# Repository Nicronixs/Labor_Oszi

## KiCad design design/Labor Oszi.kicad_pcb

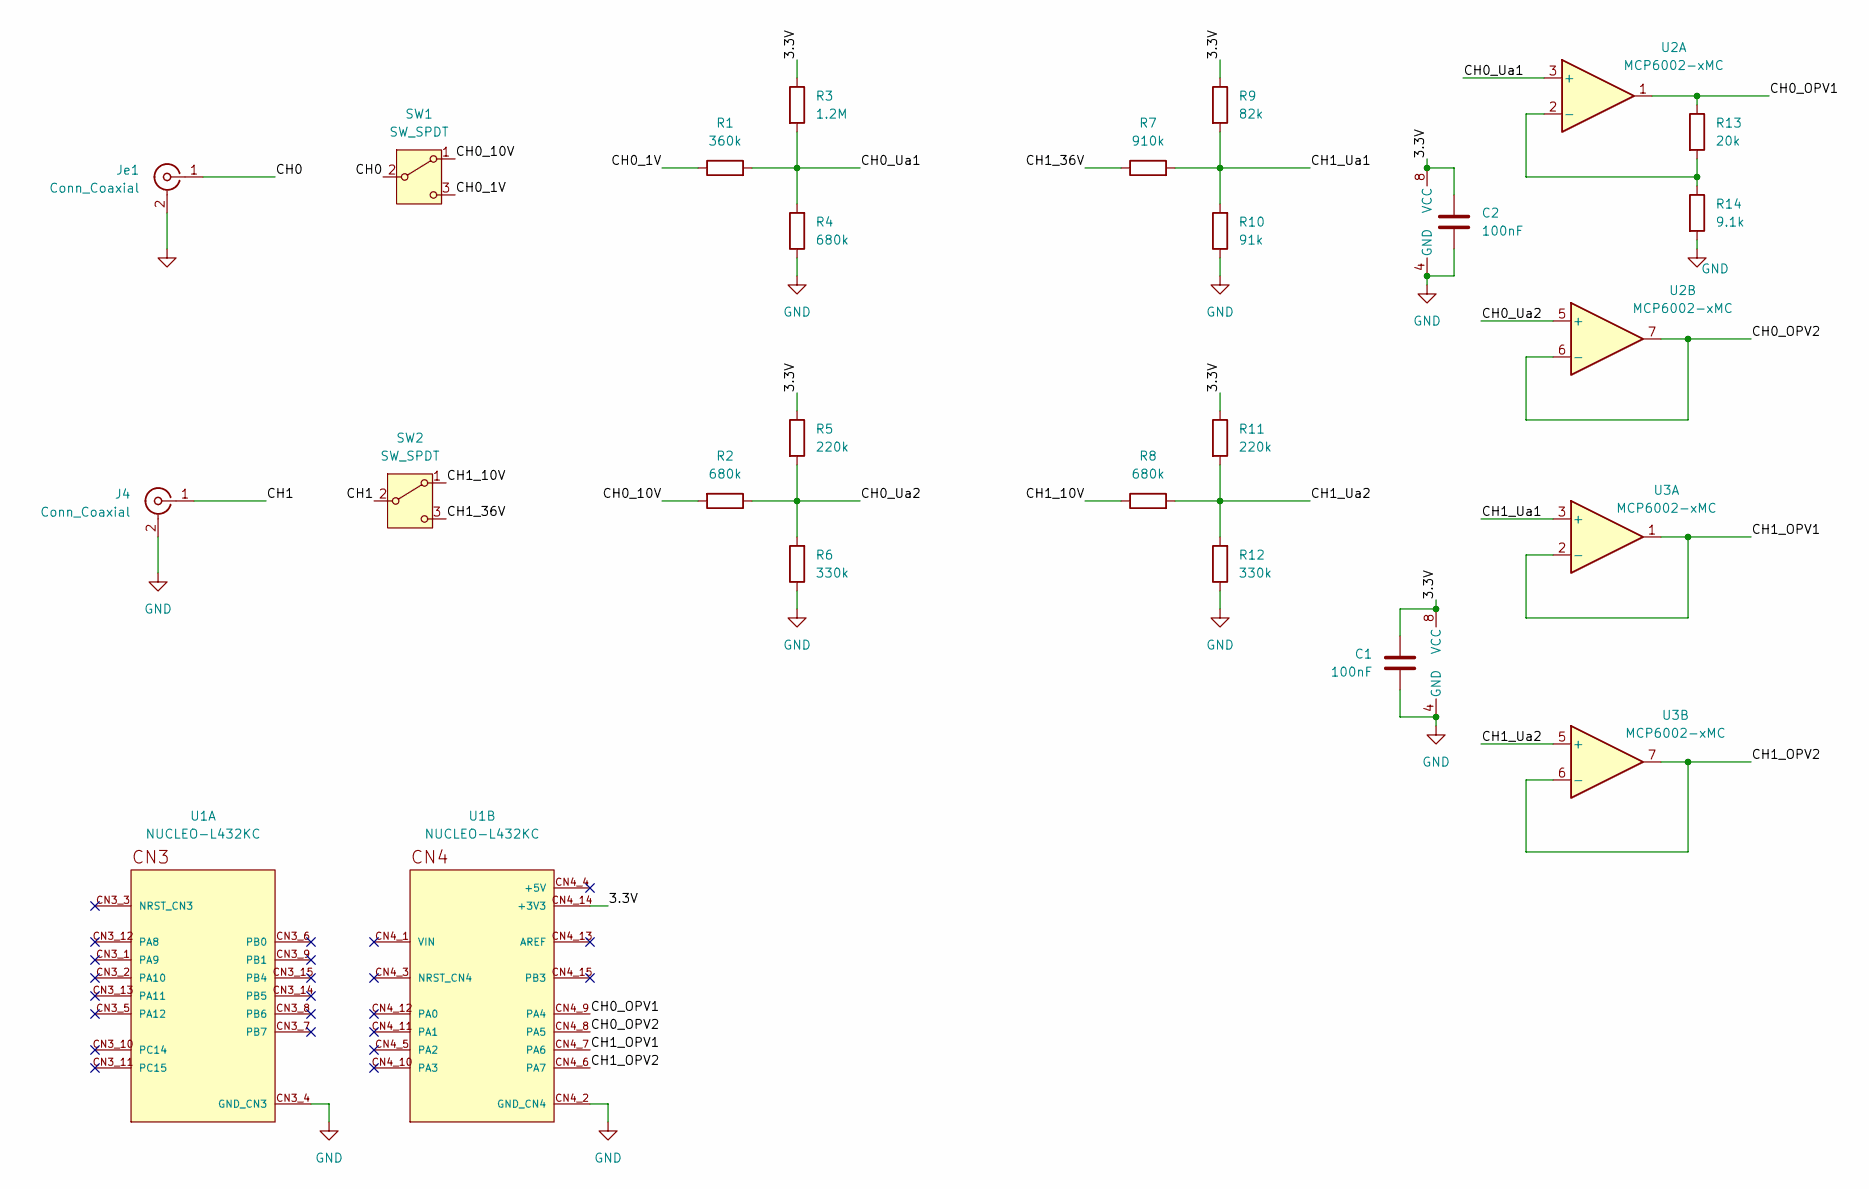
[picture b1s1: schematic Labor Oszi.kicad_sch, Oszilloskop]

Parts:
C1, C2: 100nF; C_0603_1608Metric_Pad1.08x0.95mm_HandSolder; LCSC Part # C14663
J4: Conn_Coaxial; LINX_CONBNC001
Je1: Conn_Coaxial; LINX_CONBNC001
R1: 360k; R_0603_1608Metric_Pad0.98x0.95mm_HandSolder; LCSC Part # C23146
R2, R4, R8: 680k; R_0603_1608Metric_Pad0.98x0.95mm_HandSolder; LCSC Part # C25822
R3: 1.2M; R_0603_1608Metric_Pad0.98x0.95mm_HandSolder; LCSC Part # C22107
R5, R11: 220k; R_0603_1608Metric_Pad0.98x0.95mm_HandSolder; LCSC Part # C22961
R6, R12: 330k; R_0603_1608Metric_Pad0.98x0.95mm_HandSolder; LCSC Part # C23137
R7: 910k; R_0603_1608Metric_Pad0.98x0.95mm_HandSolder; LCSC Part # C23263
R9: 82k; R_0603_1608Metric_Pad0.98x0.95mm_HandSolder; LCSC Part # C23254
R10: 91k; R_0603_1608Metric_Pad0.98x0.95mm_HandSolder; LCSC Part # C23265
R13: 20k; R_0603_1608Metric_Pad0.98x0.95mm_HandSolder; LCSC Part # C4184
R14: 9.1k; R_0603_1608Metric_Pad0.98x0.95mm_HandSolder; LCSC Part # C23260
SW1, SW2: SW_SPDT; SW_SPDT_PCM12
U1: NUCLEO-L432KC; MODULE_NUCLEO-L432KC; PARTREV N/A
U2, U3: MCP6002-xMC; DFN-8-1EP_3x2mm_P0.5mm_EP1.75x1.45mm; LCSC Part # C185041

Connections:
/3.3V: C1.1, C2.1, R3.1, R5.1, R9.1, R11.1, U1.CN4_14 (+3V3), U2.8 (VCC), U3.8 (VCC)
/CH0: Je1.1 (In), SW1.2 (B)
/CH0_1V: R1.1, SW1.3 (C)
/CH0_10V: R2.2, SW1.1 (A)
/CH0_OPV1: R13.1, U1.CN4_9 (PA4), U2.1
/CH0_OPV2: U1.CN4_8 (PA5), U2.6 (-), U2.7
/CH0_Ua1: R1.2, R3.2, R4.2, U2.3 (+)
/CH0_Ua2: R2.1, R5.2, R6.2, U2.5 (+)
/CH1: J4.1 (In), SW2.2 (B)
/CH1_10V: R8.1, SW2.1 (A)
/CH1_36V: R7.1, SW2.3 (C)
/CH1_OPV1: U1.CN4_7 (PA6), U3.1, U3.2 (-)
/CH1_OPV2: U1.CN4_6 (PA7), U3.6 (-), U3.7
/CH1_Ua1: R7.2, R9.2, R10.2, U3.3 (+)
/CH1_Ua2: R8.2, R11.2, R12.2, U3.5 (+)
GND: C1.2, C2.2, J4.2 (Ext), Je1.2 (Ext), R4.1, R6.1, R10.1, R12.1, R14.2, U1.CN3_4 (GND_CN3), U1.CN4_2 (GND_CN4), U2.4 (GND), U3.4 (GND)
unnamed: R13.2, R14.1, U2.2 (-)

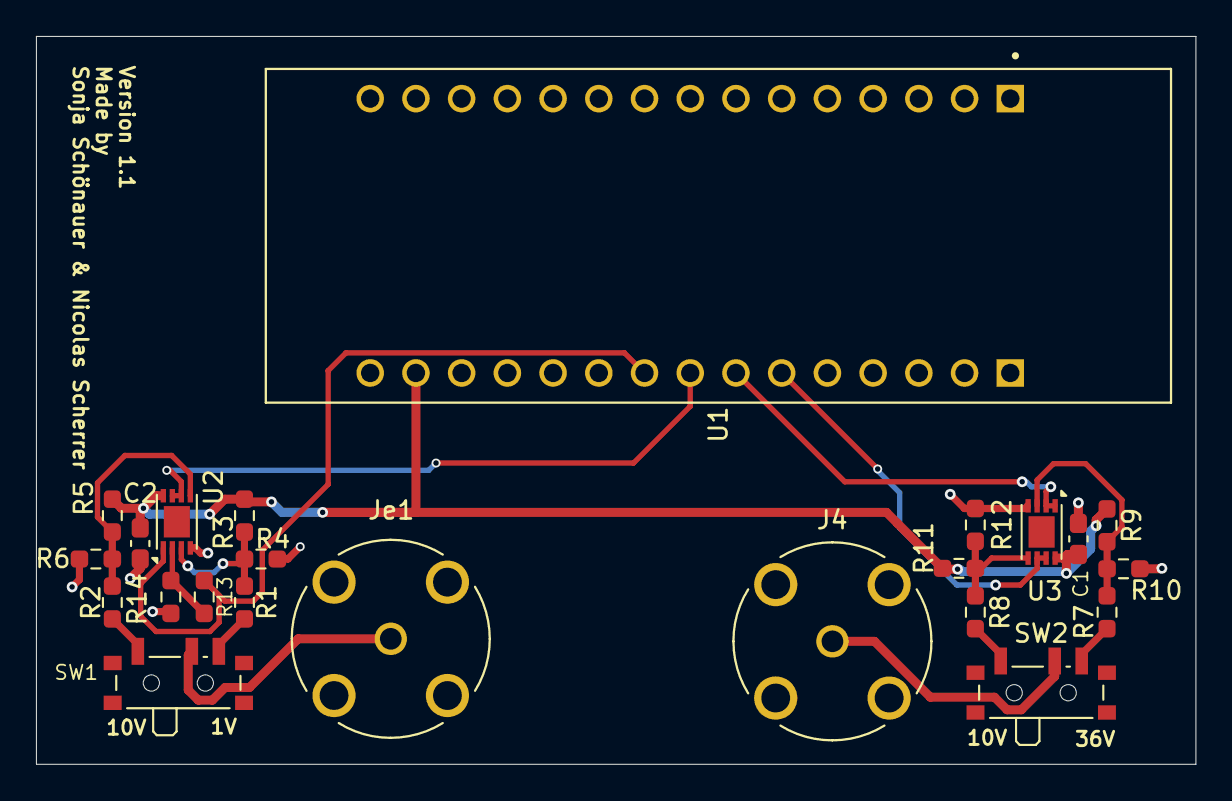
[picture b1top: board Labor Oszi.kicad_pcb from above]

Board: 2 copper layers, 64.4 x 40.4 mm, 23 parts (0 on the bottom side), 17 nets.

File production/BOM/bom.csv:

"Reference","Qty","Value","DNP","Exclude from BOM","Exclude from Board","Footprint","Datasheet","LCSC Part #"
"C1,C2","2","100nF","","","","Capacitor_SMD:C_0603_1608Metric_Pad1.08x0.95mm_HandSolder","~","C14663"
"J4,Je1","2","Conn_Coaxial","","","","CONBNC001:LINX_CONBNC001","~",""
"R1","1","360k","","","","Resistor_SMD:R_0603_1608Metric_Pad0.98x0.95mm_HandSolder","~","C23146"
"R2,R4,R8","3","680k","","","","Resistor_SMD:R_0603_1608Metric_Pad0.98x0.95mm_HandSolder","~","C25822"
"R3","1","1.2M","","","","Resistor_SMD:R_0603_1608Metric_Pad0.98x0.95mm_HandSolder","~","C22107"
"R5,R11","2","220k","","","","Resistor_SMD:R_0603_1608Metric_Pad0.98x0.95mm_HandSolder","~","C22961"
"R6,R12","2","330k","","","","Resistor_SMD:R_0603_1608Metric_Pad0.98x0.95mm_HandSolder","~","C23137"
"R7","1","910k","","","","Resistor_SMD:R_0603_1608Metric_Pad0.98x0.95mm_HandSolder","~","C23263"
"R9","1","82k","","","","Resistor_SMD:R_0603_1608Metric_Pad0.98x0.95mm_HandSolder","~","C23254"
"R10","1","91k","","","","Resistor_SMD:R_0603_1608Metric_Pad0.98x0.95mm_HandSolder","~","C23265"
"R13","1","20k","","","","Resistor_SMD:R_0603_1608Metric_Pad0.98x0.95mm_HandSolder","~","C4184"
"R14","1","9.1k","","","","Resistor_SMD:R_0603_1608Metric_Pad0.98x0.95mm_HandSolder","~","C23260"
"SW1,SW2","2","SW_SPDT","","","","Button_Switch_SMD:SW_SPDT_PCM12","~",""
"U1","1","NUCLEO-L432KC","","","","NUCLEO_L432KC:MODULE_NUCLEO-L432KC","",""
"U2,U3","2","MCP6002-xMC","","","","Package_DFN_QFN:DFN-8-1EP_3x2mm_P0.5mm_EP1.75x1.45mm","http://ww1.microchip.com/downloads/en/DeviceDoc/21733j.pdf","C185041"

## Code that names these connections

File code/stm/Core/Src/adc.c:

/* USER CODE BEGIN Header */
/**
  ******************************************************************************
  * @file    adc.c
  * @brief   This file provides code for the configuration
  *          of the ADC instances.
  ******************************************************************************
  * @attention
  *
  * Copyright (c) 2025 STMicroelectronics.
  * All rights reserved.
  *
  * This software is licensed under terms that can be found in the LICENSE file
  * in the root directory of this software component.
  * If no LICENSE file comes with this software, it is provided AS-IS.
  *
  ******************************************************************************
  */
/* USER CODE END Header */
/* Includes ------------------------------------------------------------------*/
#include "adc.h"

/* USER CODE BEGIN 0 */
ADC_HandleTypeDef hadc1;
/* USER CODE END 0 */

ADC_HandleTypeDef ;

/* ADC1 init function */
void MX_ADC1_Init(void)
{

  /* USER CODE BEGIN ADC1_Init 0 */

  /* USER CODE END ADC1_Init 0 */

  ADC_ChannelConfTypeDef sConfig = {0};

  /* USER CODE BEGIN ADC1_Init 1 */

  /* USER CODE END ADC1_Init 1 */

  /** Common config
  */
  hadc1.Instance = ADC1;
  hadc1.Init.ClockPrescaler = ADC_CLOCK_ASYNC_DIV1;
  hadc1.Init.Resolution = ADC_RESOLUTION_12B;
  hadc1.Init.DataAlign = ADC_DATAALIGN_RIGHT;
  hadc1.Init.ScanConvMode = ADC_SCAN_DISABLE;
  hadc1.Init.EOCSelection = ADC_EOC_SINGLE_CONV;
  hadc1.Init.LowPowerAutoWait = DISABLE;
  hadc1.Init.ContinuousConvMode = DISABLE;
  hadc1.Init.NbrOfConversion = 1;
  hadc1.Init.DiscontinuousConvMode = DISABLE;
  hadc1.Init.ExternalTrigConv = ADC_SOFTWARE_START;
  hadc1.Init.ExternalTrigConvEdge = ADC_EXTERNALTRIGCONVEDGE_NONE;
  hadc1.Init.DMAContinuousRequests = DISABLE;
  hadc1.Init.Overrun = ADC_OVR_DATA_PRESERVED;
  hadc1.Init.OversamplingMode = DISABLE;
  if (HAL_ADC_Init(&hadc1) != HAL_OK)
  {
    Error_Handler();
  }

  /** Configure Regular Channel
  */
  sConfig.Channel = ADC_CHANNEL_9;
  sConfig.Rank = ADC_REGULAR_RANK_1;
  sConfig.SamplingTime = ADC_SAMPLETIME_2CYCLES_5;
  sConfig.SingleDiff = ADC_SINGLE_ENDED;
  sConfig.OffsetNumber = ADC_OFFSET_NONE;
  sConfig.Offset = 0;
  if (HAL_ADC_ConfigChannel(&hadc1, &sConfig) != HAL_OK)
  {
    Error_Handler();
  }
  /* USER CODE BEGIN ADC1_Init 2 */

  /* USER CODE END ADC1_Init 2 */

}

void HAL_ADC_MspInit(ADC_HandleTypeDef* adcHandle)
{

  GPIO_InitTypeDef GPIO_InitStruct = {0};
  RCC_PeriphCLKInitTypeDef PeriphClkInit = {0};
  if(adcHandle->Instance==ADC1)
  {
  /* USER CODE BEGIN ADC1_MspInit 0 */

  /* USER CODE END ADC1_MspInit 0 */

  /** Initializes the peripherals clock
  */
    PeriphClkInit.PeriphClockSelection = RCC_PERIPHCLK_ADC;
    PeriphClkInit.AdcClockSelection = RCC_ADCCLKSOURCE_PLLSAI1;
    PeriphClkInit.PLLSAI1.PLLSAI1Source = RCC_PLLSOURCE_MSI;
    PeriphClkInit.PLLSAI1.PLLSAI1M = 1;
    PeriphClkInit.PLLSAI1.PLLSAI1N = 16;
    PeriphClkInit.PLLSAI1.PLLSAI1P = RCC_PLLP_DIV7;
    PeriphClkInit.PLLSAI1.PLLSAI1Q = RCC_PLLQ_DIV2;
    PeriphClkInit.PLLSAI1.PLLSAI1R = RCC_PLLR_DIV2;
    PeriphClkInit.PLLSAI1.PLLSAI1ClockOut = RCC_PLLSAI1_ADC1CLK;
    if (HAL_RCCEx_PeriphCLKConfig(&PeriphClkInit) != HAL_OK)
    {
      Error_Handler();
    }

    /* ADC1 clock enable */
    __HAL_RCC_ADC_CLK_ENABLE();

    __HAL_RCC_GPIOA_CLK_ENABLE();
    /**ADC1 GPIO Configuration
    PA4     ------> ADC1_IN9
    PA5     ------> ADC1_IN10
    PA6     ------> ADC1_IN11
    PA7     ------> ADC1_IN12
    */
    GPIO_InitStruct.Pin = GPIO_PIN_4|GPIO_PIN_5|GPIO_PIN_6|GPIO_PIN_7;
    GPIO_InitStruct.Mode = GPIO_MODE_ANALOG_ADC_CONTROL;
    GPIO_InitStruct.Pull = GPIO_NOPULL;
    HAL_GPIO_Init(GPIOA, &GPIO_InitStruct);

  /* USER CODE BEGIN ADC1_MspInit 1 */

  /* USER CODE END ADC1_MspInit 1 */
  }
}

void HAL_ADC_MspDeInit(ADC_HandleTypeDef* adcHandle)
{

  if(adcHandle->Instance==ADC1)
  {
  /* USER CODE BEGIN ADC1_MspDeInit 0 */

  /* USER CODE END ADC1_MspDeInit 0 */
    /* Peripheral clock disable */
    __HAL_RCC_ADC_CLK_DISABLE();

    /**ADC1 GPIO Configuration
    PA4     ------> ADC1_IN9
    PA5     ------> ADC1_IN10
    PA6     ------> ADC1_IN11
    PA7     ------> ADC1_IN12
    */
    HAL_GPIO_DeInit(GPIOA, GPIO_PIN_4|GPIO_PIN_5|GPIO_PIN_6|GPIO_PIN_7);

  /* USER CODE BEGIN ADC1_MspDeInit 1 */

  /* USER CODE END ADC1_MspDeInit 1 */
  }
}

/* USER CODE BEGIN 1 */

/* USER CODE END 1 */

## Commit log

2025-11-28 test
2025-12-05 Python Plotten
2025-12-05 stm32 code
2025-12-12 Schaltplan Revision
2025-12-12 Protokoll added
2025-12-12 Code versioniert
2025-12-12 minor Part changes & Folder Structure fixes
2025-12-12 stm code
2025-12-12 minor changes on the pcb
2025-12-19 } error fixed
2026-01-09 Protokoll updated
2026-01-09 deleted random numbers in cube code
